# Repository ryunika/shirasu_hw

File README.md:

# shirasu_hw
shirasu_fwのwikiを見てください.
releaseからガーバーファイルとJLCPCBのSMT用のデータが手に入ります.

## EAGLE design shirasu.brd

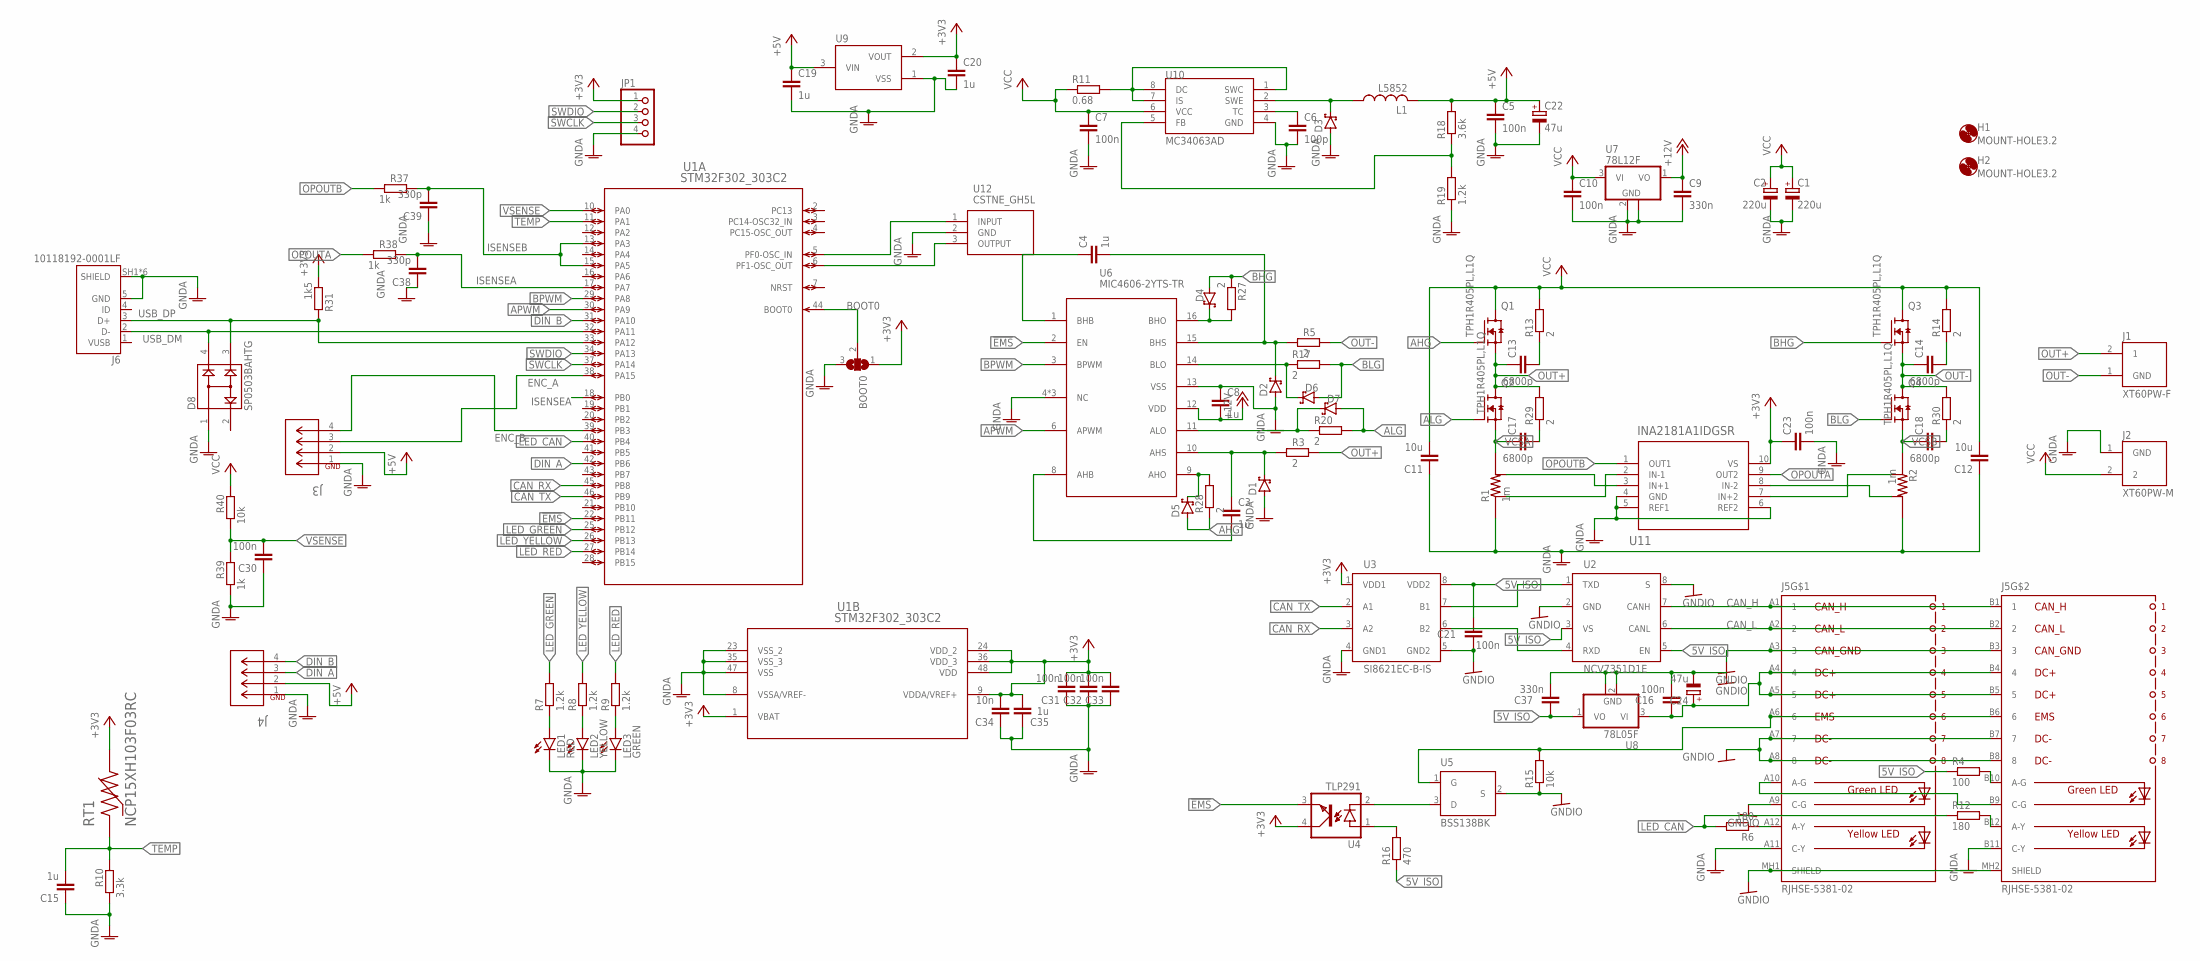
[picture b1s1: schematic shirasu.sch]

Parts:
BOOT0: SJ2W; SJ_2
C1, C2: 220u; E5-10,5
C3, C4, C8, C15, C19, C20, C35: 1u; C0603
C5, C7, C10, C16, C21, C23, C30, C31, C32, C33: 100n; C0603
C6: 100p; C0603
C9, C37: 330n; C0603
C11, C12: 10u; C1210
C13, C14, C17, C18: 6800p; C0603
C22, C24: 47u; E2,5-5
C34: 10n; C0603
C38, C39: 330p; C0603
D1, D2, D3, D4, D5, D6, D7: PMEG6010CEJ,115; SOD323_ST
D8: SP0503BAHTG; SOT143
H1, H2: MOUNT-HOLE3.2; 3,2
J1: XT60PW-F; AMASS_XT60PW-F
J2: XT60PW-M; AMASS_XT60PW-M
J3, J4: EP2.5-4-SIDE; CONN4_1744426-4
J5: RJHSE-5381-02; RJHSE538102
J6: 10118192-0001LF; AMPHENOL_10118192-0001LF
JP1: PINHD-1X4; 1X04
L1: L5852
LED1: RED; CHIP-LED0603
LED2: YELLOW; CHIP-LED0603
LED3: GREEN; CHIP-LED0603
Q1, Q2, Q3, Q4: TPH1R405PL,L1Q; SOPADVANCE
R1, R2: 1m; 2512-4PAD
R3, R5, R13, R14, R17, R20, R27, R28, R29, R30: 2; R0603
R4: 100; R0603
R6, R12: 180; R0603
R7, R8, R9, R19: 1.2k; R0603
R10: 3.3k; R0603
R11: 0.68; R1206
R15, R40: 10k; R0603
R16: 470; R0603
R18: 3.6k; R0603
R31: 1k5; R0603
R37, R38, R39: 1k; R0603
RT1: NCP15XH103F03RC; THRMC1005X55N
U1: STM32F302_303C2; LQFP48-7X7MM
U2: NCV7351D1E; SO08
U3: SI8621EC-B-IS; SO08
U4: TLP291; MINI-FLAT-4
U5: BSS138BK; SOT23
U6: MIC4606-2YTS-TR; TSSOP16
U7: 78L12F; SOT89
U8: 78L05F; SOT89
U9: XC6206; SOT95P240X110-3
U10: MC34063AD; SOIC8
U11: INA2181A1IDGSR; DGS10
U12: CSTNE_GH5L

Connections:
5V_ISO: C21.2, C37.1, R4.1, R16.1, U2.3 (VS), U2.5 (EN), U3.8 (VDD2), U8.1 (VO)
!EMS: U1.22 (PB11), U4.3 (EMIT), U6.2 (EN)
+3V3: BOOT0.1, C20.1, C23.1, C31.2, C32.2, C33.2, C34.2, C35.2, JP1.1, R31.1, RT1.2, U1.1 (VBAT), U1.9 (VDDA/VREF+), U1.24 (VDD_2), U1.36 (VDD_3), U1.48 (VDD), U3.1 (VDD1), U4.4 (COL), U9.2 (VOUT), U11.10 (VS)
+5V: C5.1, C19.1, C22.+, J3.2, J4.2, L1.P$2 (2), R18.2, U9.3 (VIN)
+12V: C8.2, C9.1, U6.12 (VDD), U7.1 (VO)
AHG: D5.A, Q1.4 (G), R28.1
ALG: D7.A, Q2.4 (G), R20.2
APWM: U1.30 (PA9), U6.6 (APWM)
BHG: D4.A, Q3.4 (G), R27.1
BLG: D6.A, Q4.4 (G), R17.2
BOOT0: BOOT0.2, U1.44 (BOOT0)
BPWM: U1.29 (PA8), U6.3 (BPWM)
CAN_H: J5.A1 (1), J5.B1 (1), U2.7 (CANH)
CAN_L: J5.A2 (2), J5.B2 (2), U2.6 (CANL)
CAN_RX: U1.45 (PB8), U3.3 (A2)
CAN_TX: U1.46 (PB9), U3.2 (A1)
DIN_A: J4.3, U1.42 (PB6)
DIN_B: J4.4, U1.31 (PA10)
ENC_A: J3.3, U1.38 (PA15)
ENC_B: J3.4, U1.39 (PB3)
GNDA: BOOT0.3, C1.-, C2.-, C5.2, C6.2, C7.2, C8.1, C9.2, C10.2, C11.1, C12.1, C15.1, C19.2, C20.2, C22.-, C23.2, C30.1, C31.1, C32.1, C33.1, C34.1, C35.1, C38.1, C39.1, D1.A, D2.A, D3.A, D8.1, J2.1 (GND), J3.1, J4.1, J5.A11 (C-Y), J5.B11 (C-Y), J6.5 (GND), J6.SH1 (SHIELD), J6.SH2 (SHIELD), J6.SH3 (SHIELD), J6.SH4 (SHIELD), J6.SH5 (SHIELD), J6.SH6 (SHIELD), JP1.4, LED1.C, LED2.C, LED3.C, R1.1, R1.2 (1), R2.3 (2), R2.4 (2), R10.1, R19.1, R39.1, U1.8 (VSSA/VREF-), U1.23 (VSS_2), U1.35 (VSS_3), U1.47 (VSS), U3.4 (GND1), U6.4 (NC), U6.5 (NC), U6.7 (NC), U6.13 (VSS), U7.2 (GND), U7.2@1 (GND), U9.1 (VSS), U10.4 (GND), U11.4 (GND), U11.5 (REF1), U11.6 (REF2), U12.2 (GND)
GNDIO: C16.2, C21.1, C24.-, C37.2, J5.A3 (3), J5.A7 (7), J5.A8 (8), J5.A9 (C-G), J5.B3 (3), J5.B7 (7), J5.B8 (8), J5.MH1 (SHIELD), J5.MH2 (SHIELD), R15.1, U2.2 (GND), U2.8 (S), U3.5 (GND2), U5.2 (S), U8.2 (GND), U8.2@1 (GND)
ISENSEA: C38.2, R38.2, U1.17 (PA7), U1.18 (PB0)
ISENSEB: C39.2, R37.2, U1.13 (PA3), U1.15 (PA5)
LED_CAN: R6.2, R12.1, U1.40 (PB4)
LED_GREEN: R7.2, U1.25 (PB12)
LED_RED: R9.2, U1.27 (PB14)
LED_YELLOW: R8.2, U1.26 (PB13)
unnamed: C17.2, R29.1
unnamed: C18.2, R30.1
unnamed: C3.1, D1.C, R3.1, U6.10 (AHS)
unnamed: C3.2, U6.8 (AHB)
unnamed: C4.2, D2.C, R5.1, U6.15 (BHS)
unnamed: J5.B10 (A-G), R4.2
unnamed: J5.A10 (A-G), J5.B9 (C-G)
unnamed: C4.1, U6.1 (BHB)
unnamed: LED1.A, R7.1
unnamed: LED2.A, R8.1
unnamed: LED3.A, R9.1
unnamed: J5.A12 (A-Y), R6.1
unnamed: J5.B12 (A-Y), R12.2
unnamed: U2.1 (TXD), U3.7 (B1)
unnamed: C16.1, C24.+, J5.A4 (4), J5.A5 (5), J5.B4 (4), J5.B5 (5), U8.3 (VI)
unnamed: U2.4 (RXD), U3.6 (B2)
unnamed: J5.A6 (6), J5.B6 (6), R15.2, U5.1 (G)
unnamed: C14.2, R14.1
unnamed: D6.C, R17.1, U6.14 (BLO)
unnamed: C13.2, R13.1
unnamed: D7.C, R20.1, U6.11 (ALO)
unnamed: R1.6 (4), U11.3 (IN+1)
unnamed: R2.5 (3), U11.7 (IN+2)
unnamed: U4.2 (C), U5.3 (D)
unnamed: R16.2, U4.1 (A)
unnamed: D3.C, L1.P$1 (1), U10.2 (SWE)
unnamed: C6.1, U10.3 (TC)
unnamed: R18.1, R19.2, U10.5 (FB)
unnamed: R2.6 (4), U11.8 (IN-2)
unnamed: R11.2, U10.1 (SWC), U10.7 (IS), U10.8 (DC)
unnamed: R1.5 (3), U11.2 (IN-1)
unnamed: D4.C, R27.2, U6.16 (BHO)
unnamed: D5.C, R28.2, U6.9 (AHO)
unnamed: U1.5 (PF0-OSC_IN), U12.1 (INPUT)
unnamed: U1.6 (PF1-OSC_OUT), U12.3 (OUTPUT)
OPOUTA: R38.1, U11.9 (OUT2)
OPOUTB: R37.1, U11.1 (OUT1)
OUT+: C13.1, J1.2 (1), Q1.1 (S), Q1.2 (S), Q1.3 (S), Q2.5 (D), Q2.6 (D), Q2.7 (D), Q2.8 (D), Q2.9 (D), R3.2, R29.2
OUT-: C14.1, J1.1 (GND), Q3.1 (S), Q3.2 (S), Q3.3 (S), Q4.5 (D), Q4.6 (D), Q4.7 (D), Q4.8 (D), Q4.9 (D), R5.2, R30.2
SWCLK: JP1.3, U1.37 (PA14)
SWDIO: JP1.2, U1.34 (PA13)
TEMP: C15.2, R10.2, RT1.1, U1.11 (PA1)
USB_DM: D8.4, J6.2 (D-), U1.32 (PA11)
USB_DP: D8.3, J6.3 (D+), R31.2, U1.33 (PA12)
VCC: C1.+, C2.+, C7.1, C10.1, C11.2, C12.2, J2.2, Q1.5 (D), Q1.6 (D), Q1.7 (D), Q1.8 (D), Q1.9 (D), Q3.5 (D), Q3.6 (D), Q3.7 (D), Q3.8 (D), Q3.9 (D), R11.1, R13.2, R14.2, R40.2, U7.3 (VI), U10.6 (VCC)
VCSA: C17.1, Q2.1 (S), Q2.2 (S), Q2.3 (S), R1.3 (2), R1.4 (2)
VCSB: C18.1, Q4.1 (S), Q4.2 (S), Q4.3 (S), R2.1, R2.2 (1)
VSENSE: C30.2, R39.2, R40.1, U1.10 (PA0)

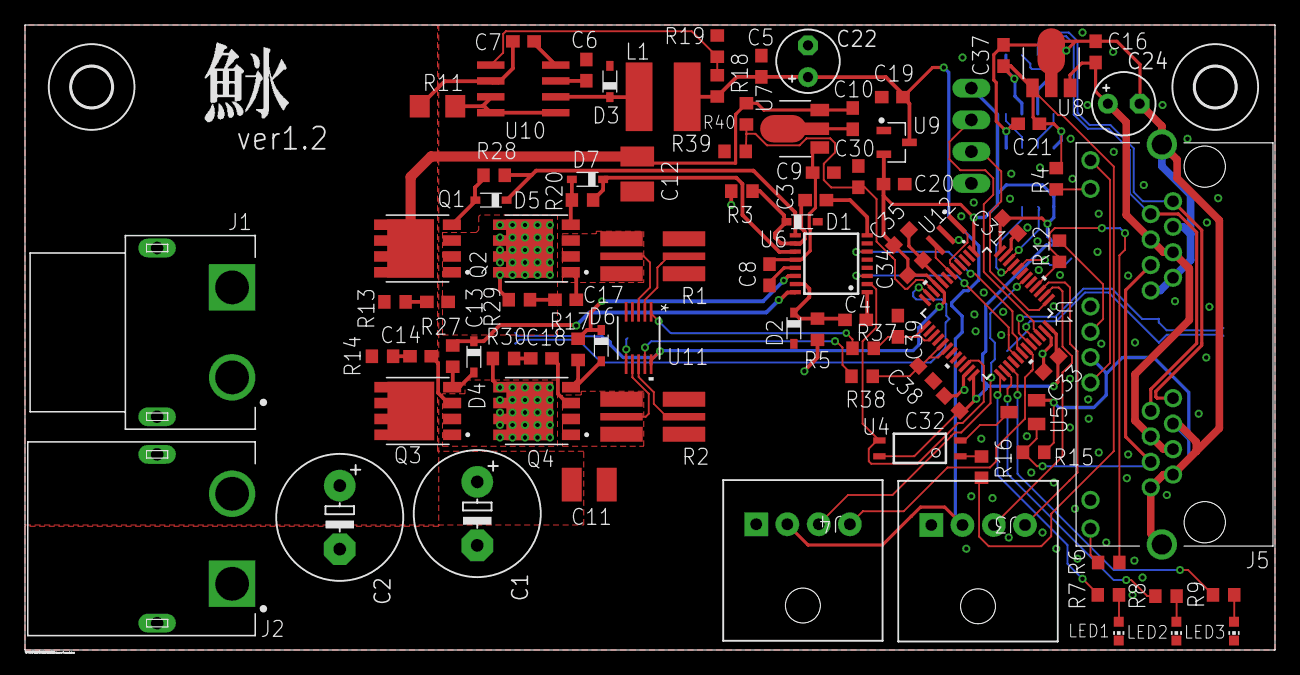
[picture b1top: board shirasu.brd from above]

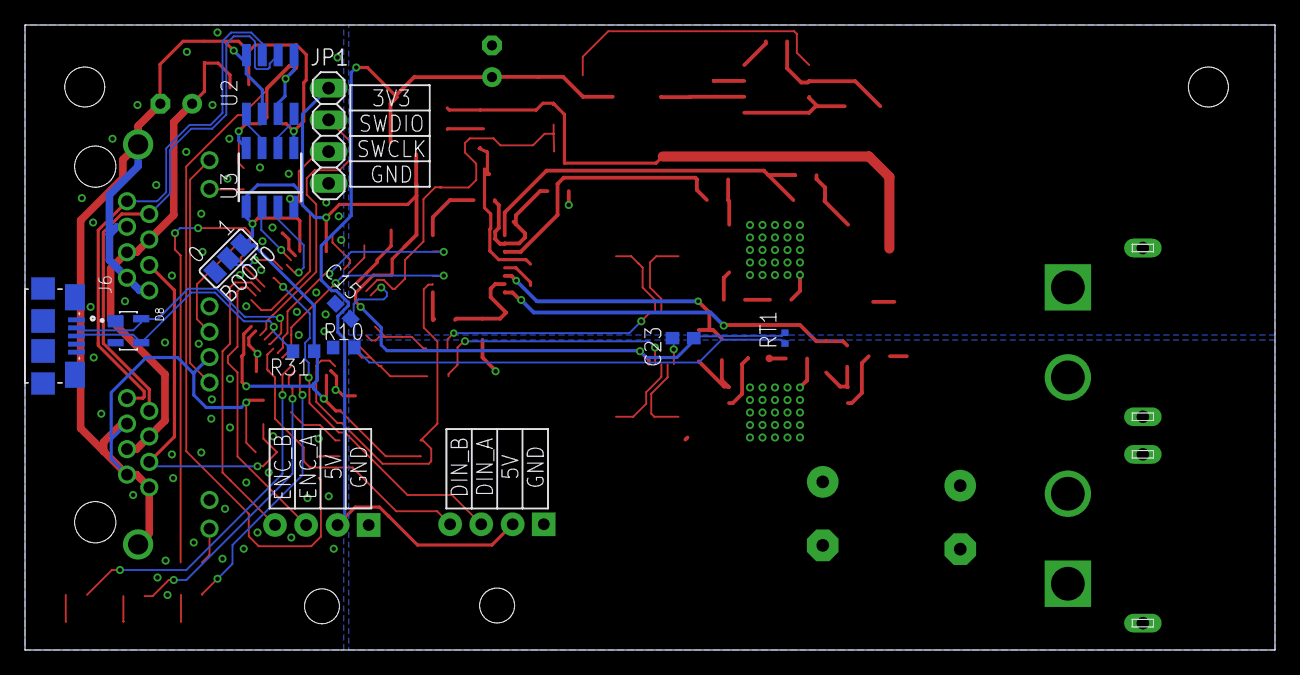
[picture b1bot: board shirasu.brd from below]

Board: 2 copper layers, 100.0 x 50.0 mm, 101 parts (11 on the bottom side), 76 nets.

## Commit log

2020-11-01 fixed xt connector removed some resistors and capacitors
2020-12-20 ver1.0
2020-12-30 use TIM1 for pwm instead of TIM15,add gate resistors for low side MOSFET as well.
2021-01-17 BOMを追加
2021-01-17 csvファイルも追加
2021-04-27 ver1.2

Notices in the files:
parts and their libraries:
COPYRIGHT: Copyright (C) 2016 Accelerated Designs. All rights reserved
COPYRIGHT: Copyright (C) 2018 Accelerated Designs. All rights reserved
